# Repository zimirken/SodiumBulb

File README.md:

# SodiumBulb
low pressure sodium vapor bulb
This is designed to drive a GP20NA or GP20ND low pressure sodium vapor bulb. 

These bulbs normally run on 15-20 volts at 1-2 amps. However, ignition is much more difficult. They require an ignition pulse of >400 volts with oomph behind it for a second or two in order to jump the gap between the main electrodes. This made designing a compact battery powered driver very difficult.

There is only one step up transformer in the circuit that serves dual purposes. During normal operation the secondary is disconnected and the primary is used as an inductor in a boost converter to generate the 15-20 volts to power the lamp. However during ignition, relays connect the secondary of the transformer to the bulb, and then the primary is driven HARD to get a discharge going across the electrode gap. The transformer and mosfet will overheat rapidly during this, but it only takes a couple seconds. It's also quite fun, as it gives you the feeling of igniting a flame lantern. When the lamp isn't ignited, the boost converter maintains the capacitor voltage at 35 volts. This extra voltage buffer gives the bulb a bit of extra juice to keep it lit while switching from ignite to drive.

The transformer was salvaged from a power supply, should be about a 10x step up. A transformer from one of those chinese 12V to 350V DC-DC boost converter boards should work. You will have to experiment with bulb polarity when hooking it to the circuit, Mine ignited much easier one way vs the other. NOT SHOWN on the schematic(but shown in pictures) is an inductor in series with the bulb. It's literally a coil of wire around an 8mm steel bolt. For me it made the bulb less likely to go out randomly, but wasn't required. In fact it looks like I might have not even included it in the final build. There's an enable terminal block, and an ignite terminal block. Jump the enable pins to enable the whole thing. Put a pushbutton switch on the ignite pins for igniting the bulb. The circuit and program has built in low voltage cutoff.

The 12 volt power in doesn't have its own connector on the boards, it is connected to pins 1(gnd) and 2(12v) on the GPG terminal block on the power board. Study the schematic and pictures to confirm.

Bulb: https://www.aliexpress.us/item/2255801048097192.html

A step file for the lantern assembly I built is included, but likely won't be super helpful. It's based on an outdoor house lamp I found at a thrift store.

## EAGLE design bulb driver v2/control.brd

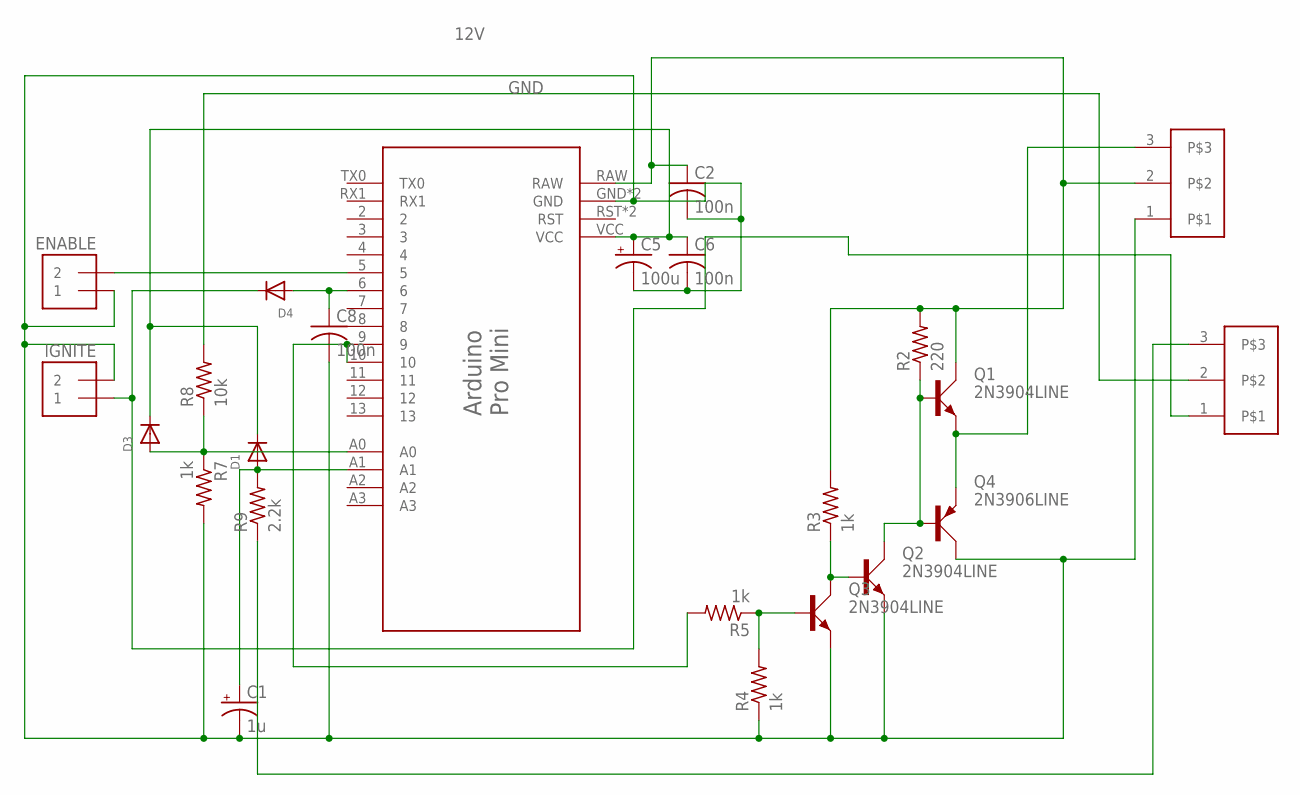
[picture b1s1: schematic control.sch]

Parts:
C1: 1u; E2,5-6
C2: 100n; C050-030X075
C5: 100u; E2,5-6
C6, C8: 100n; C050-025X075
D1, D3, D4: DIODEDO-1N4148; DO-1N4148
ENABLE: 1X2_12PINS; 1X2PINS
GPG: 1X3_123
IGNITE: 1X2_12HORZPINS; 1X2HORZ
IVI: 1X3_123
Q1, Q2, Q3: 2N3904LINE; TO92-LINE
Q4: 2N3906LINE; TO92-LINE
R2: 220; 0204/5
R3, R4: 1k; 0207/2V
R5: 1k; 0207/15
R7: 1k; 0207/5V
R8: 10k; 0207/15
R9: 2.2k; 0207/12
U$1: PRO_MINI

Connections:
12V: C2.1, GPG.2, Q1.C, R2.2, R3.2, U$1.RAW
GND: C1.-, C2.2, C5.-, C6.2, C8.2, ENABLE.1, GPG.1, IGNITE.2, Q2.E, Q3.E, Q4.C, R4.1, R7.2, U$1.GND, U$1.GND1 (GND)
unnamed: D3.A, R7.1, R8.1, U$1.A0
unnamed: C5.+, C6.1, D1.C, D3.C, U$1.VCC
unnamed: GPG.3, Q1.E, Q4.E
unnamed: Q3.B, R4.2, R5.1
unnamed: Q1.B, Q2.C, Q4.B, R2.1
unnamed: Q2.B, Q3.C, R3.1
unnamed: R5.2, U$1.9, U$1.10
unnamed: C1.+, D1.A, R9.2, U$1.A1
unnamed: IVI.3, R9.1
unnamed: IVI.2, R8.2
unnamed: ENABLE.2, U$1.5
unnamed: C8.1, D4.A, U$1.6
unnamed: D4.C, IGNITE.1, IVI.1

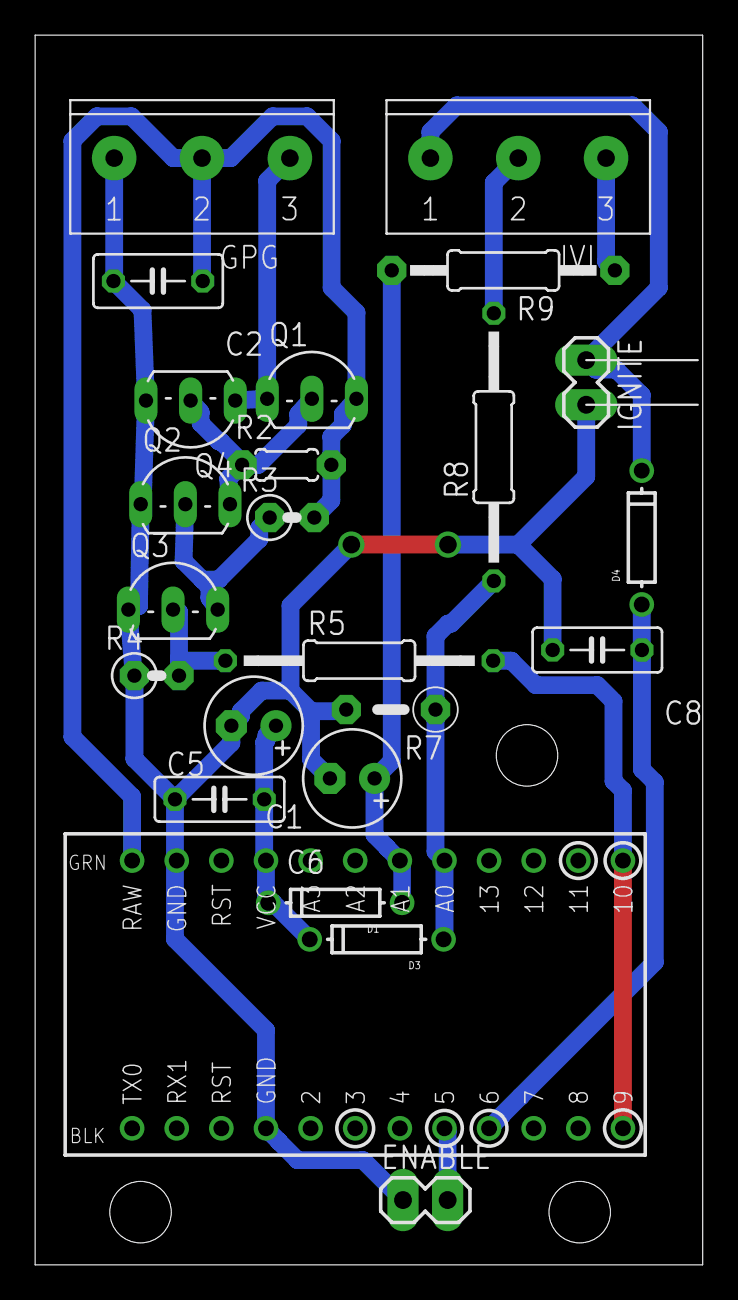
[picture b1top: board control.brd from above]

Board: 2 copper layers, 38.0 x 70.0 mm, 24 parts (0 on the bottom side), 15 nets.

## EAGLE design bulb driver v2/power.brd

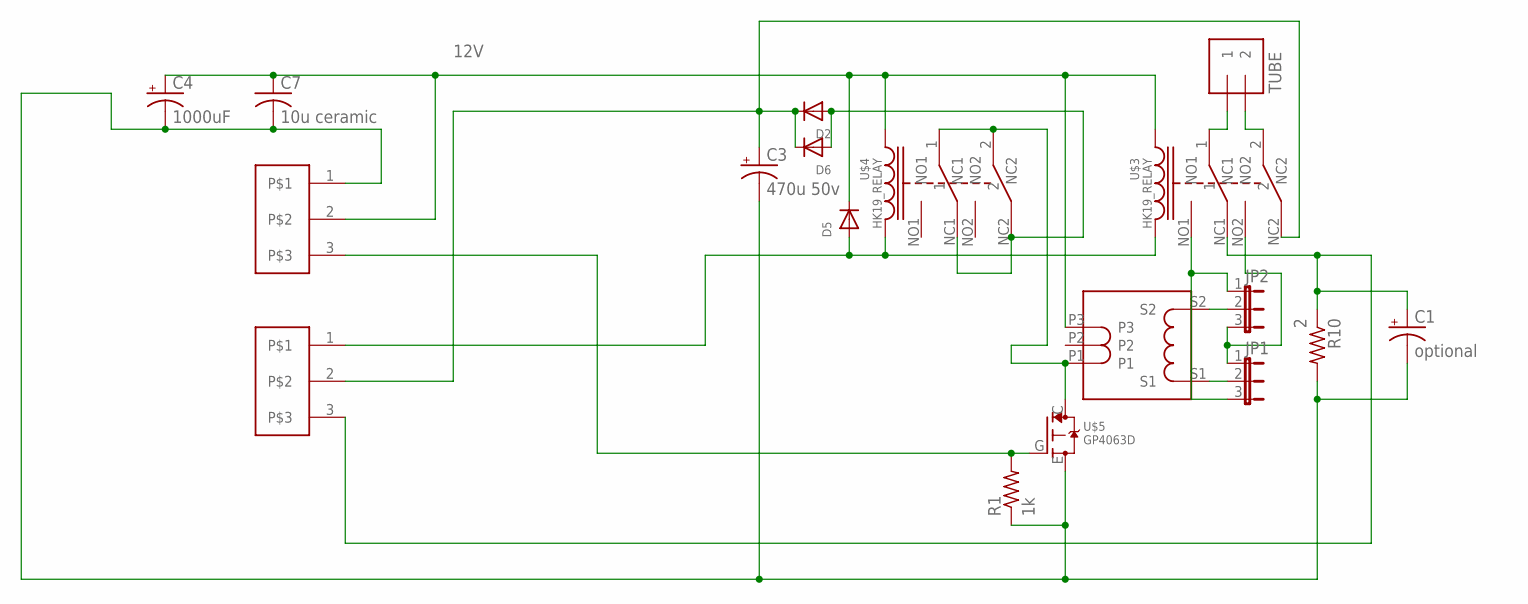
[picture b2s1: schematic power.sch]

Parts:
C1: optional; E2,5-6
C3: 470u 50v; E5-10,5
C4: 1000uF; E5-10,5
C7: 10u ceramic; C050-045X075
D2, D5, D6: DIODEDO-1N4148; DO-1N4148
GPG: 1X3_123
IVC: 1X3_123
JP1, JP2: JP2E; JP2
R1: 1k; 0204V
R10: 2; P0817V
TUBE: 1X2_1221; 1X2_21
U$2: TRANSFORMER_RAND_1
U$3, U$4: HK19_RELAY; HK19RELAY
U$5: GP4063D; TO247

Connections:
12V: C4.+, C7.1, D5.C, GPG.2, U$2.P3, U$3.C1, U$4.C1
GND: C1.-, C3.-, C4.-, C7.2, GPG.1, R1.1, R10.2, U$5.E
unnamed: TUBE.1, U$3.1
unnamed: TUBE.2, U$3.2
unnamed: JP2.2, U$2.S2
unnamed: JP1.2, U$2.S1
unnamed: U$2.P1, U$4.1, U$4.2, U$5.C
unnamed: GPG.3, R1.2, U$5.G
unnamed: JP1.3, JP2.1, U$3.NO1
unnamed: JP1.1, JP2.3, U$3.NO2
unnamed: D2.A, D6.A, U$4.NC1, U$4.NC2
unnamed: C1.+, IVC.3, R10.1, U$3.NC1
unnamed: C3.+, D2.C, D6.C, IVC.2, U$3.NC2
unnamed: D5.A, IVC.1, U$3.C2, U$4.C2

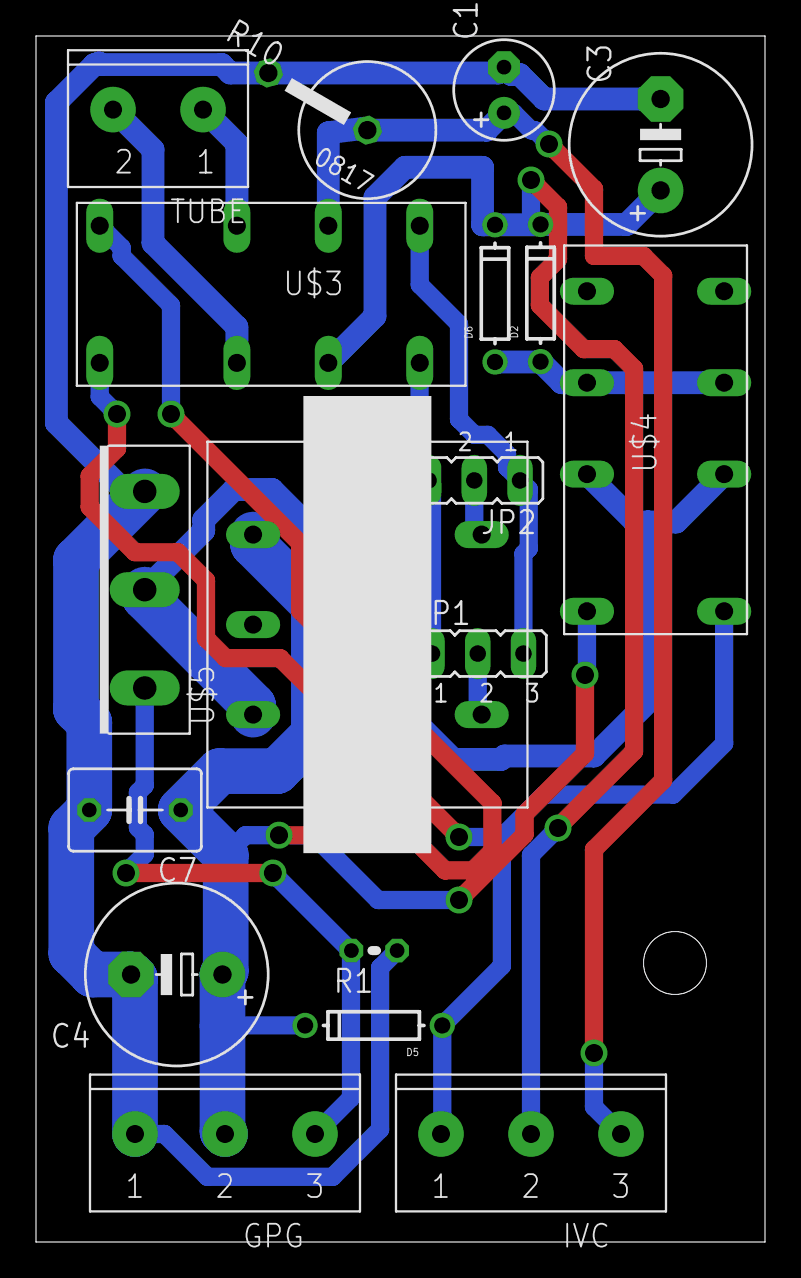
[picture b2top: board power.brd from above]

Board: 2 copper layers, 40.5 x 67.0 mm, 18 parts (0 on the bottom side), 14 nets.
